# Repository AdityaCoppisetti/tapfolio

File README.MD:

## here is how the pcb looks like -

HEY! So im dhruv coppisetti and im a fellow hackcluber like you guys! Ive been the cameraman for hack club Delhi for the past 3 events- daydream, campfire and build guild. 
Every person i meet and every event i go to, people think i am just a cameraman, AS IF I DONT KNOW ANYTHING IN ROBOTICS!!!bahahaha  
 
in build guild delhi my team did this incredibly creative thing where we 3d printed badges and put nfc tags behind them and we would program then to show anything we want like our insta profiles so we could connect with people in a fun way or show people our graphic designing portfolios. For me it was my photography portfolio - 

 https://portraitmode.io/profile/dhruv-coppisetti/ 

And so shortly after that event i was doing this marketing internship where i was setting up stalls in places in other cities and in my home city aswell. I would meet tons of people! Even customers that wanted to buy products would be great for networking as i would set up stalls in tech company buildings. Even the people in their own stalls beside mine would be extremely beneficial to network!  

after build guild i took a nfc fob I got with my robotics kit and programmed it to open my portfolio link. But that was just one portfolio out of – robotics, psychology, poetry, filmmaking and photography. And so thus began the ponder “ do i carry 6 different key fobs with me or what” i ended up with the conclusion that i need a creative and cool nfc portfolio badge that could be good to start conversations and impress the people im networking with ( basically make a lasting impression). And so, i decided – i would make something wearable around my neck, add a screen to it and buttons and make it look like a built it in a cave. 

LIKE COME ON GITHUB FOLLOWS THE SAME THING WITH THEIR E INK BADGES (only, that badge is incredibly expensive to get, but not to make. 
 
here is my vision for the badge ( i can't draw for shit so ill describe it, you’ll have to use your imaginations for this one) -   
 
for the nfc reader and writer i thought that the “blue PN5180 Nfc Rf Sensor Iso15693 Rfid High Frequency IC Card Icode2” would do my work and it would look cool but i later found  
“PN532 NFC RFID Reader Writer Module V0.0.1” and it was small, compact and good with reading and writing.  
 
so thats our nfc reader and writer module secured. 
 
now onto the official microcontroller. 
 
for this  
For this specific project, im leaning with the raspberry pi pico 

okay so here is the schematic + components im using!

i also want this to be battery powered and so my plan is - 

Power System 

This device is powered by a single 3.7V 500mAh lithium-polymer battery, chosen for its compact size and ease of integration into a handheld enclosure. 

Battery charging is handled by a TP4056 charging module, allowing the device to be recharged through USB while also providing battery protection features such as overcharge and overdischarge protection. 

Since the battery voltage varies during operation, a dedicated ME6211 low-dropout regulator is used to provide a stable 3.3V supply for the ESP32, OLED display, and PN532 NFC module. 

The design intentionally prioritizes simplicity and portability, using a minimal power architecture that keeps component count low while providing sufficient runtime for everyday use. 

however i wanted to use the tp4056 , i couldnt find the symbol in the kicad library , now i could just download it from somewhere but whats the fun in that so i decided to make my own , you can find the documentation for that in the journal.md

 here how the lithium battery charging module i made!

the components- 

and how my pcb looks like - 

it is really really compact

# how to assemble 

after you receive the parts + pcb 

you take your solder stencil and then put the solder paste all over the required area  and then you use the footprints to place the components on the required area and then you reflow them using a hotplate or a hot blow air gun. 

and then for the main pcb , everything is labelled really neatly where you have to put them 

# how to use 

there are 3 buttons , the right button you use to go up your nfc profiles list, the left button you use to go down your profile list and then the middle button is to select and write the nfc profile 
its that simple

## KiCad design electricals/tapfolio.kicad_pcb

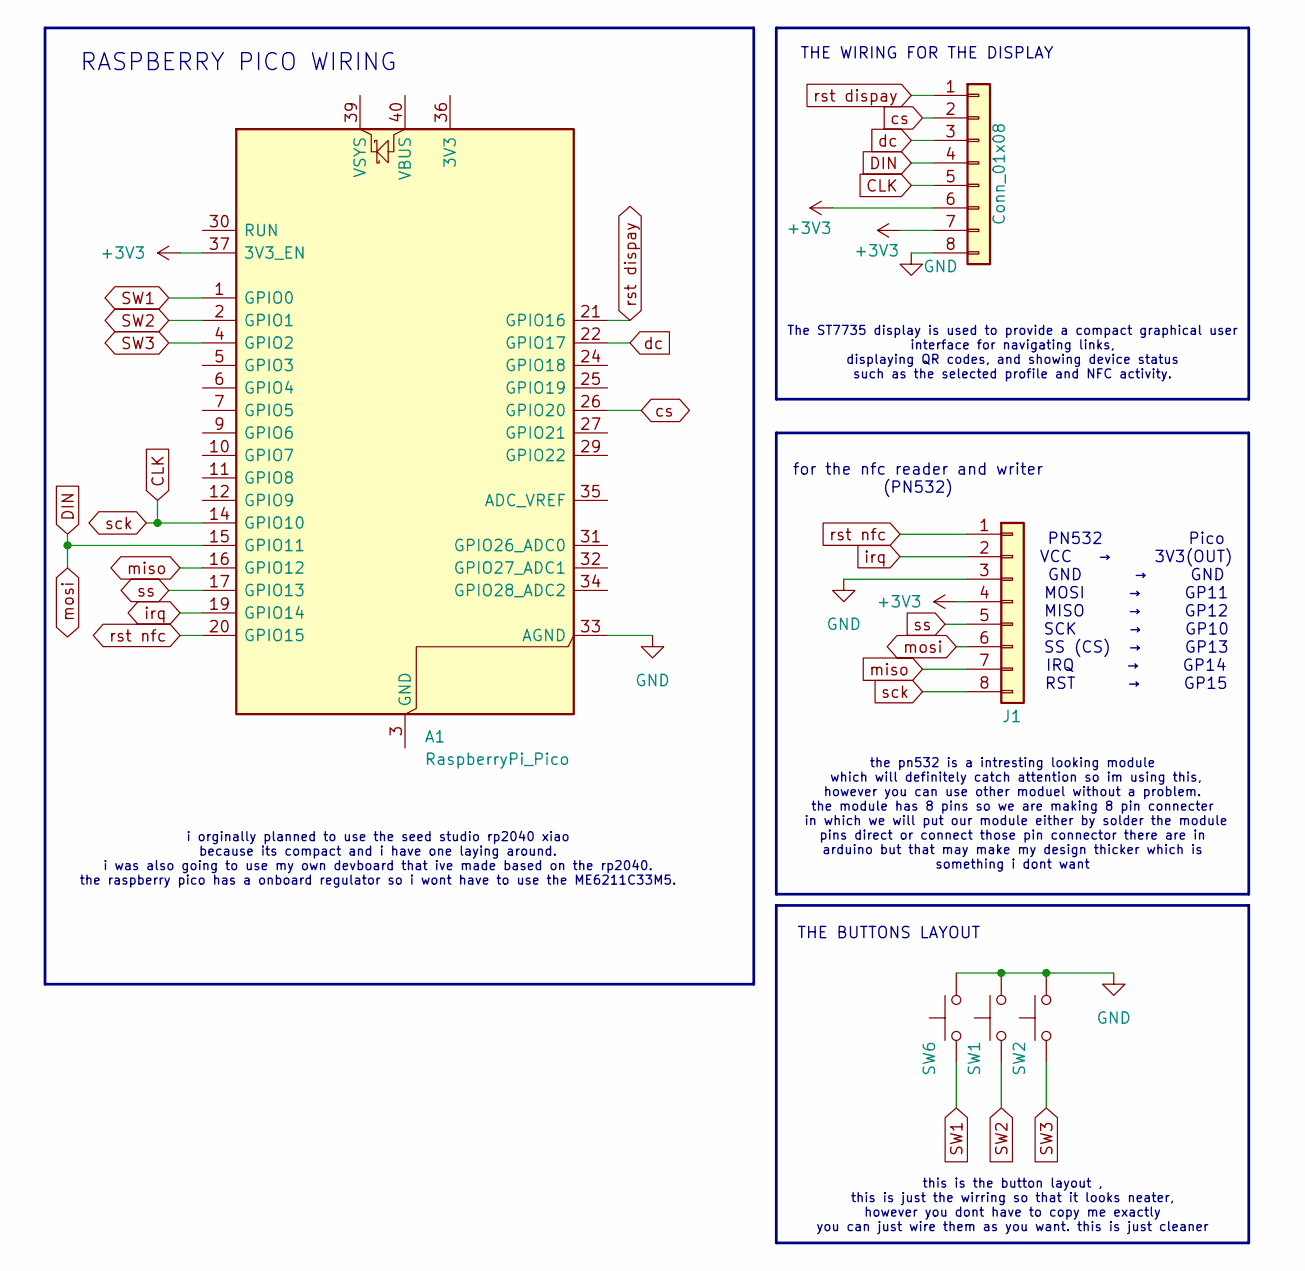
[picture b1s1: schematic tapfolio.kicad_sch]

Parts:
A1: RaspberryPi_Pico; RaspberryPi_Pico_Common_THT
J1, J2: Conn_01x08; PinHeader_1x08_P2.54mm_Vertical
SW1, SW2, SW6: SW_Push; SW_SPST_TL3342

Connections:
+3V3: A1.37 (3V3_EN), J1.4, J2.6, J2.7
CLK: A1.14 (GPIO10), J1.8, J2.5
DIN: A1.15 (GPIO11), J1.6, J2.4
GND: A1.33 (AGND), J1.3, J2.8, SW1.2, SW2.2, SW6.2
unnamed: A1.3 (GND), A1.8 (GND), A1.13 (GND), A1.18 (GND), A1.23 (GND), A1.28 (GND), A1.38 (GND)
SW1: A1.1 (GPIO0), SW6.1
SW2: A1.2 (GPIO1), SW1.1
SW3: A1.4 (GPIO2), SW2.1
cs: A1.26 (GPIO20), J2.2
dc: A1.22 (GPIO17), J2.3
irq: A1.19 (GPIO14), J1.2
miso: A1.16 (GPIO12), J1.7
rst dispay: A1.21 (GPIO16), J2.1
rst nfc: A1.20 (GPIO15), J1.1
ss: A1.17 (GPIO13), J1.5

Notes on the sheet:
the pn532 is a intresting looking module which will definitely catch attention so im using this, however you can use other moduel without a problem. the module has 8 pins so we are making 8 pin connecter in which we will put our module either by solder the module pins direct or connect those pin co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
i orginally planned to use the seed studio rp2040 xiao because its compact and i have one laying around. i was also going to use my own devboard that ive made based on the rp2040. the raspberry pico has a onboard regulator so i wont have to use the ME6211C33M5.
RASPBERRY PICO WIRING
THE BUTTONS LAYOUT
this is the button layout , this is just the wirring so that it looks neater, however you dont have to copy me exactly you can just wire them as you want. this is just cleaner
THE WIRING FOR THE DISPLAY
PN532 Pico VCC → 3V3(OUT) GND → GND MOSI → GP11 MISO → GP12 SCK → GP10 SS (CS) → GP13 IRQ → GP14 RST → GP15
for the nfc reader and writer (PN532)
The ST7735 display is used to provide a compact graphical user interface for navigating links, displaying QR codes, and showing device status such as the selected profile and NFC activity.

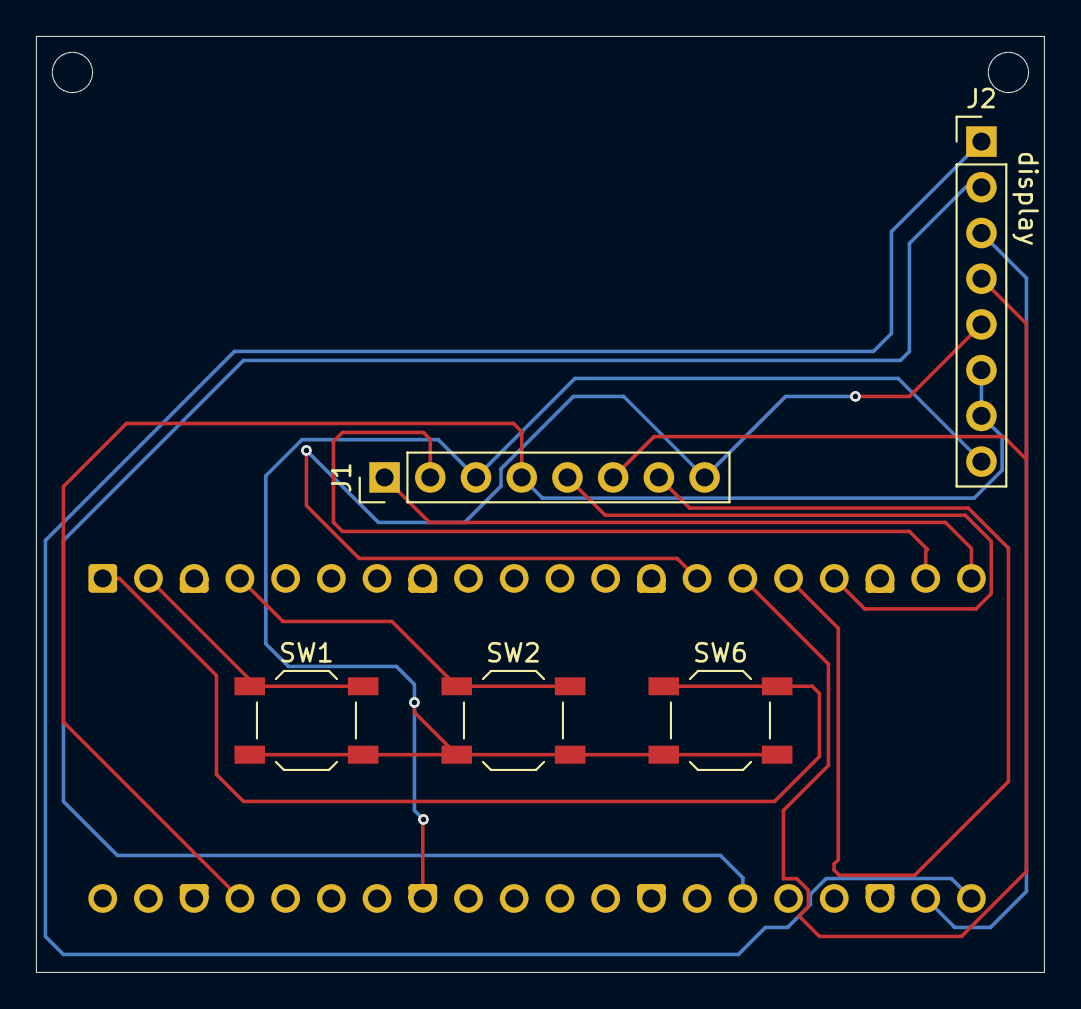
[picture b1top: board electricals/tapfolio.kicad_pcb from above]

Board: 2 copper layers, 56.0 x 52.0 mm, 6 parts (1 on the bottom side), 15 nets.

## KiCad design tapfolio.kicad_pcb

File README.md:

//
#

#

here is how the pcb looks like - 

HEY! So im dhruv coppisetti and im a fellow hackcluber like you guys! Ive been the cameraman for hack club Delhi for the past 3 events- daydream, campfire and build guild. 
Every person i meet and every event i go to, people think i am just a cameraman, AS IF I DONT KNOW ANYTHING IN ROBOTICS!!!bahahaha  
 
in build guild delhi my team did this incredibly creative thing where we 3d printed badges and put nfc tags behind them and we would program then to show anything we want like our insta profiles so we could connect with people in a fun way or show people our graphic designing portfolios. For me it was my photography portfolio - 

 https://portraitmode.io/profile/dhruv-coppisetti/ 

And so shortly after that event i was doing this marketing internship where i was setting up stalls in places in other cities and in my home city aswell. I would meet tons of people! Even customers that wanted to buy products would be great for networking as i would set up stalls in tech company buildings. Even the people in their own stalls beside mine would be extremely beneficial to network!  

after build guild i took a nfc fob I got with my robotics kit and programmed it to open my portfolio link. But that was just one portfolio out of – robotics, psychology, poetry, filmmaking and photography. And so thus began the ponder “ do i carry 6 different key fobs with me or what” i ended up with the conclusion that i need a creative and cool nfc portfolio badge that could be good to start conversations and impress the people im networking with ( basically make a lasting impression). And so, i decided – i would make something wearable around my neck, add a screen to it and buttons and make it look like a built it in a cave. 

LIKE COME ON GITHUB FOLLOWS THE SAME THING WITH THEIR E INK BADGES (only, that badge is incredibly expensive to get, but not to make. 
 
here is my vision for the badge ( i can't draw for shit so ill describe it, you’ll have to use your imaginations for this one) -   
 
for the nfc reader and writer i thought that the “blue PN5180 Nfc Rf Sensor Iso15693 Rfid High Frequency IC Card Icode2” would do my work and it would look cool but i later found  
“PN532 NFC RFID Reader Writer Module V0.0.1” and it was small, compact and good with reading and writing.  
 
so thats our nfc reader and writer module secured. 
 
now onto the official microcontroller. 
 
for this  
For this specific project, im leaning with the raspberry pi pico 

okay so here is the schematic + components im using!

i also want this to be battery powered and so my plan is - 

Power System 

This device is powered by a single 3.7V 500mAh lithium-polymer battery, chosen for its compact size and ease of integration into a handheld enclosure. 

Battery charging is handled by a TP4056 charging module, allowing the device to be recharged through USB while also providing battery protection features such as overcharge and overdischarge protection. 

Since the battery voltage varies during operation, a dedicated ME6211 low-dropout regulator is used to provide a stable 3.3V supply for the ESP32, OLED display, and PN532 NFC module. 

The design intentionally prioritizes simplicity and portability, using a minimal power architecture that keeps component count low while providing sufficient runtime for everyday use. 

however i wanted to use the tp4056 , i couldnt find the symbol in the kicad library , now i could just download it from somewhere but whats the fun in that so i decided to make my own , you can find the documentation for that in the journal.md

 here how the lithium battery charging module i made!

the components- 

and how my pcb looks like - 

it is really really compact

 this project has taught me:-
 
 1) schematics
 2) pcb making 
 3) the evil task of routing 
 4) cad (this is also evil i just cant prove it)
 5) and then documentation
 6) the rest i kinda already knew but i did become better at it

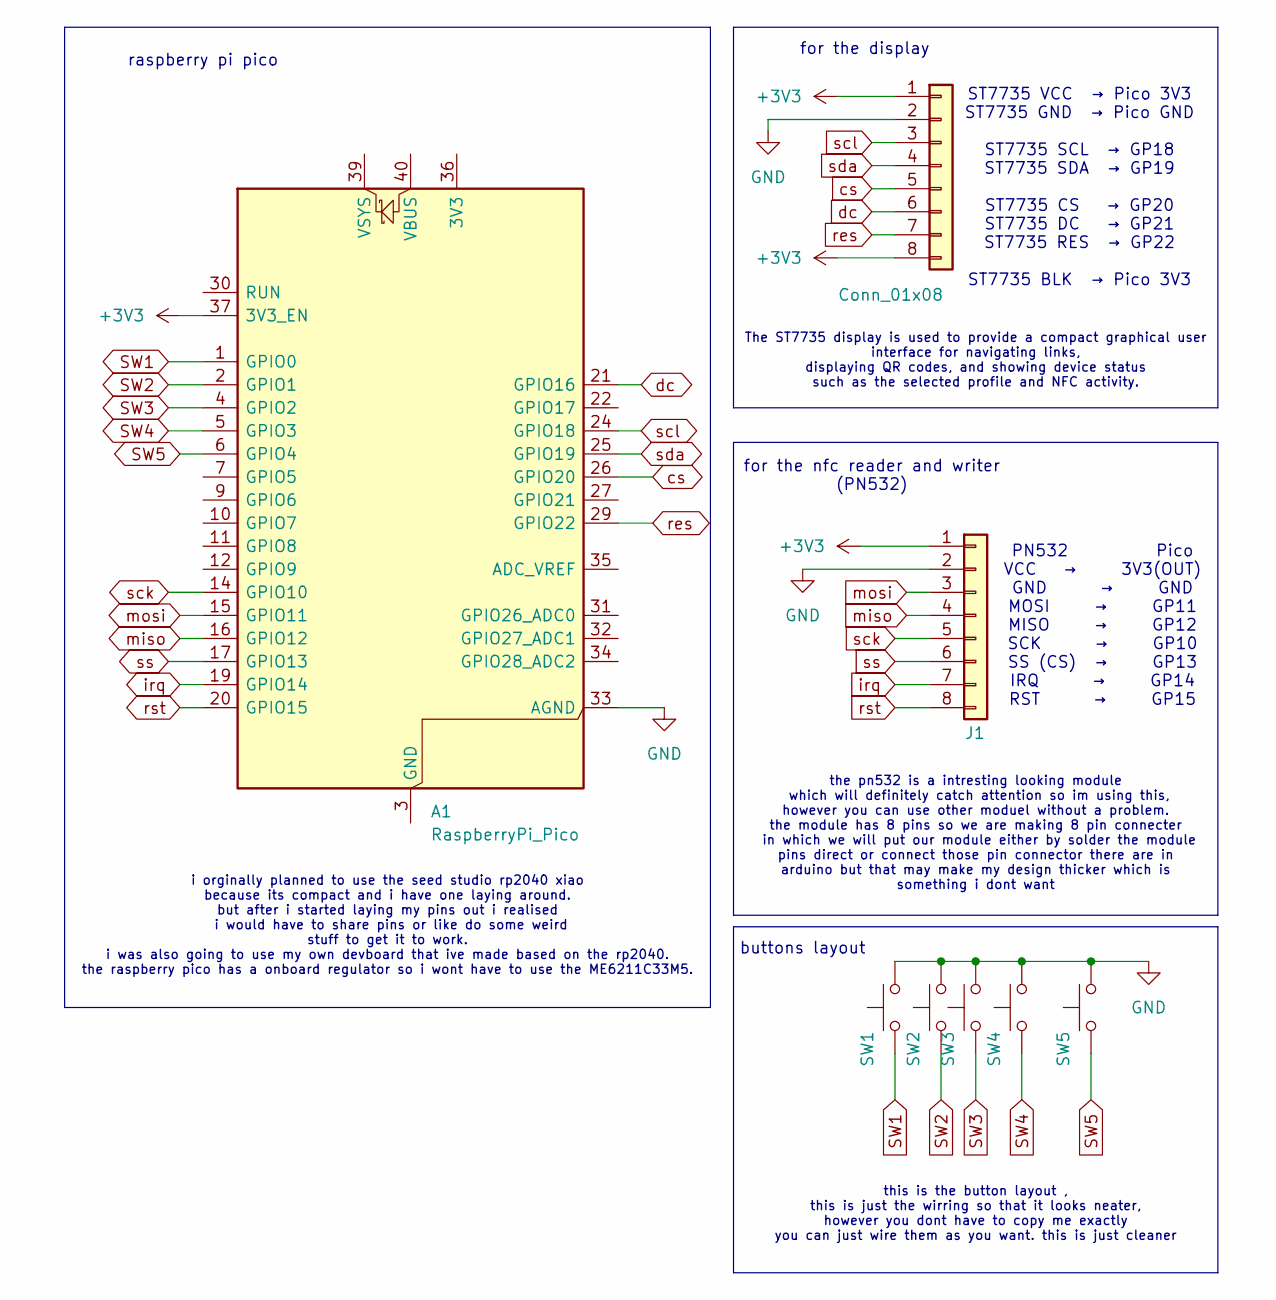
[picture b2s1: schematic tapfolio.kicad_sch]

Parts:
A1: RaspberryPi_Pico; RaspberryPi_Pico_Common_THT
J1, J2: Conn_01x08; PinHeader_1x08_P2.54mm_Vertical
SW1, SW2, SW3, SW4, SW5: SW_Push; SW_SPST_TL3342

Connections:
+3V3: A1.37 (3V3_EN), J1.1, J2.1, J2.8
GND: A1.33 (AGND), J1.2, J2.2, SW1.2, SW2.2, SW3.2, SW4.2, SW5.2
unnamed: A1.3 (GND), A1.8 (GND), A1.13 (GND), A1.18 (GND), A1.23 (GND), A1.28 (GND), A1.38 (GND)
SW1: A1.1 (GPIO0), SW1.1
SW2: A1.2 (GPIO1), SW2.1
SW3: A1.4 (GPIO2), SW3.1
SW4: A1.5 (GPIO3), SW4.1
SW5: A1.6 (GPIO4), SW5.1
cs: A1.26 (GPIO20), J2.5
dc: A1.21 (GPIO16), J2.6
irq: A1.19 (GPIO14), J1.7
miso: A1.16 (GPIO12), J1.4
mosi: A1.15 (GPIO11), J1.3
res: A1.29 (GPIO22), J2.7
rst: A1.20 (GPIO15), J1.8
sck: A1.14 (GPIO10), J1.5
scl: A1.24 (GPIO18), J2.3
sda: A1.25 (GPIO19), J2.4
ss: A1.17 (GPIO13), J1.6

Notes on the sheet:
the pn532 is a intresting looking module which will definitely catch attention so im using this, however you can use other moduel without a problem. the module has 8 pins so we are making 8 pin connecter in which we will put our module either by solder the module pins direct or connect those pin co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
ST7735 VCC → Pico 3V3 ST7735 GND → Pico GND ST7735 SCL → GP18 ST7735 SDA → GP19 ST7735 CS → GP20 ST7735 DC → GP21 ST7735 RES → GP22 ST7735 BLK → Pico 3V3
i orginally planned to use the seed studio rp2040 xiao because its compact and i have one laying around. but after i started laying my pins out i realised i would have to share pins or like do some weird stuff to get it to work. i was also going to use my own devboard that ive made based on the rp2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
raspberry pi pico
buttons layout
this is the button layout , this is just the wirring so that it looks neater, however you dont have to copy me exactly you can just wire them as you want. this is just cleaner
for the display
PN532 Pico VCC → 3V3(OUT) GND → GND MOSI → GP11 MISO → GP12 SCK → GP10 SS (CS) → GP13 IRQ → GP14 RST → GP15
for the nfc reader and writer (PN532)
The ST7735 display is used to provide a compact graphical user interface for navigating links, displaying QR codes, and showing device status such as the selected profile and NFC activity.

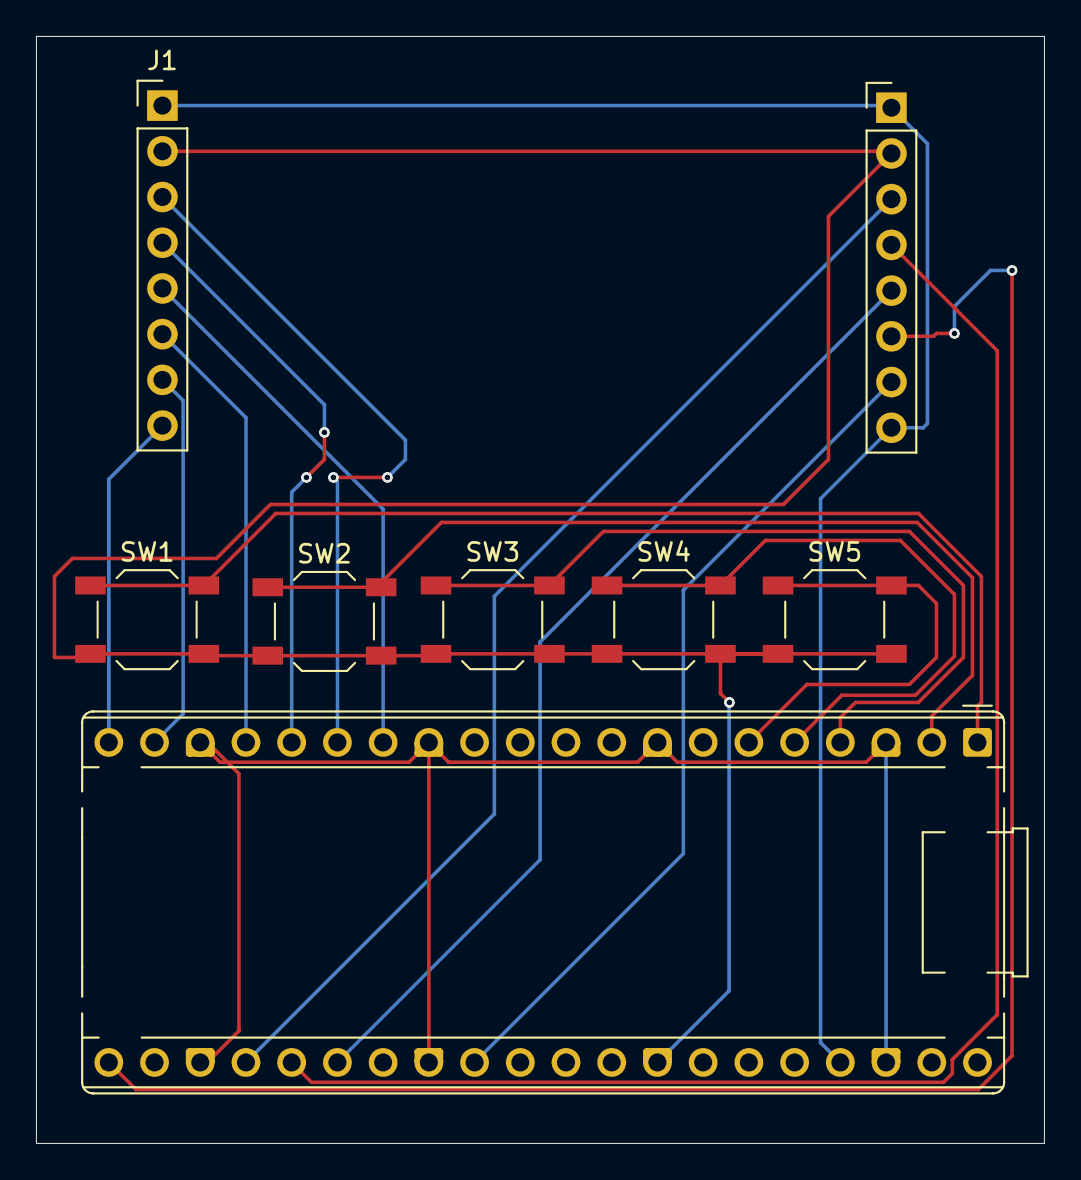
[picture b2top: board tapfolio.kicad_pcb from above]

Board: 2 copper layers, 56.0 x 61.5 mm, 8 parts (0 on the bottom side), 19 nets.

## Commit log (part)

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2026-06-07 Revise README with project details and component list
    Expanded project description and detailed components for an NFC portfolio badge, including advantages of using ESP32, power system design, and cost breakdown.
2026-06-07 Create journal.md
    journaling my progress
2026-06-30 Insert PCB 3D view image in journal
    Added a 3D view image of the PCB to the journal.
